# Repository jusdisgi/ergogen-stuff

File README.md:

# ergogen-stuff
My random ergogen files

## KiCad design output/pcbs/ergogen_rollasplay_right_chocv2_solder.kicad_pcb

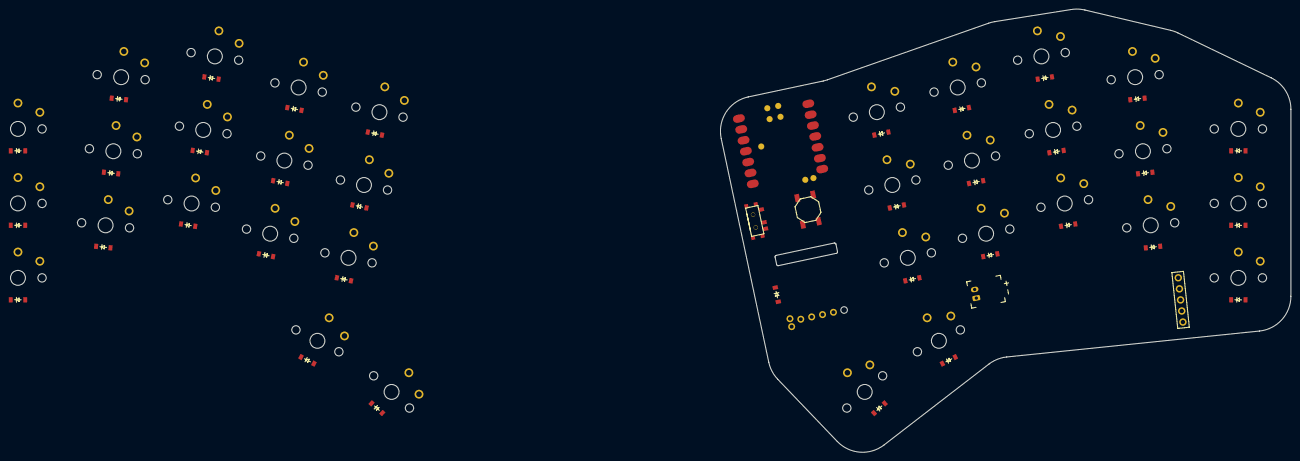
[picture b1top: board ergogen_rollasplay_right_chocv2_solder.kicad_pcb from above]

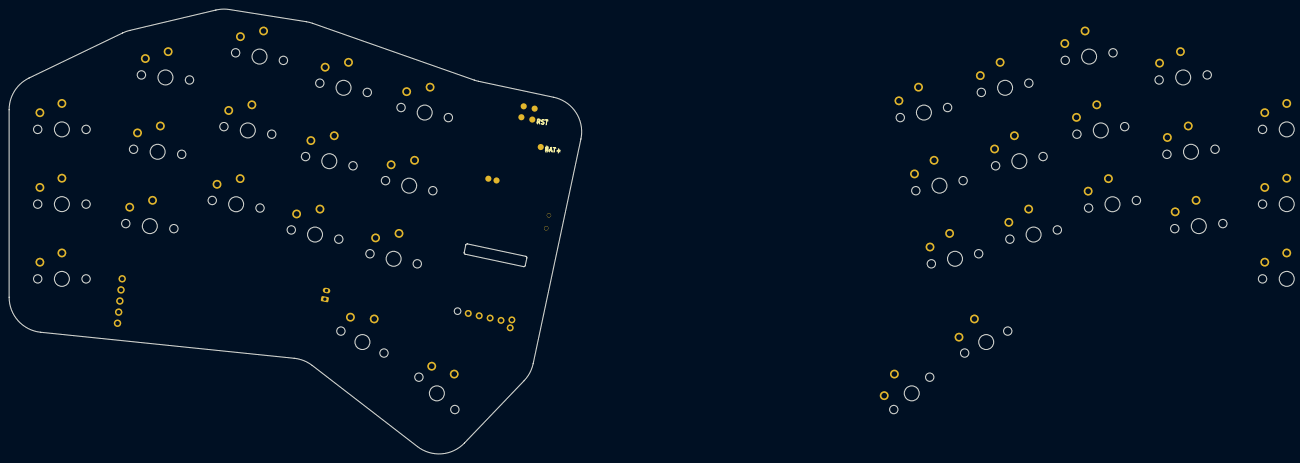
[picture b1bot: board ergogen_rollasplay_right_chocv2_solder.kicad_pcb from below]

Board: 2 copper layers, 130.2 x 101.2 mm, 74 parts (34 on the bottom side), 45 nets, no tracks yet.

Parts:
B1: SW_TACT_ALPS_SKQGABE010
D1, D2, D3, D4, D5, D6, D7, D8, D9, D10, D11, D12, D13, D14, D15, D16, D17, D18, D19, D20, D21, D22, D23, D24, D25, D26, D27, D28, D29, D30, D31, D32, D33, D34, D35: diode_tht_sod123
DISP1: display_nice_view
JST1: battery_connector_jst_ph_2
MCU1: xiao_smd
S1, S2, S3, S4, S5, S6, S7, S8, S9, S10, S11, S12, S13, S14, S15, S16, S17, S18, S19, S20, S21, S22, S23, S24, S25, S26, S27, S28, S29, S30, S31, S32, S33, S34: switch_choc_v1_v2
T1: SPDT_C128955

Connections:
D0: MCU1.1, S1.2, S2.2, S3.2, S30.2, S31.2, S32.2
D1: D3.1, D6.1, D9.1, D12.1, D15.1, MCU1.2, S27.2, S28.2, S29.2, S34.2
D2: MCU1.3, S4.2, S5.2, S6.2, S24.2, S25.2, S26.2, S33.2
D3: D2.1, D5.1, D8.1, D11.1, D14.1, MCU1.4, S21.2, S22.2, S23.2
D4: D18.1, D21.1, D24.1, D27.1, D30.1, MCU1.5, S7.2, S8.2, S9.2
D5: D1.1, D4.1, D7.1, D10.1, D13.1, D33.1, D34.1, D35.1, MCU1.6, S16.2
D8: MCU1.9, S10.2, S11.2, S12.2, S17.2, S18.2, S19.2, S20.2
D9: D19.1, D22.1, D25.1, D28.1, D31.1, MCU1.10, S13.2, S14.2, S15.2
D10: D16.1, D17.1, D20.1, D23.1, D26.1, D29.1, D32.1, MCU1.11
GND: B1.1, JST1.1, MCU1.13, MCU1.18
RST: B1.2, MCU1.17
far_onerow: D17.2, S17.1
index_bottom: D10.2, S10.1
index_home: D11.2, S11.1
index_top: D12.2, S12.1
inner_bottom: D13.2, S13.1
inner_home: D14.2, S14.1
inner_top: D15.2, S15.1
middle_bottom: D7.2, S7.1
middle_home: D8.2, S8.1
middle_top: D9.2, S9.1
mirror_far_onerow: D34.2, S34.1
mirror_index_bottom: D27.2, S27.1
mirror_index_home: D28.2, S28.1
mirror_index_top: D29.2, S29.1
mirror_inner_bottom: D30.2, S30.1
mirror_inner_home: D31.2, S31.1
mirror_inner_top: D32.2, S32.1
mirror_middle_bottom: D24.2, S24.1
mirror_middle_home: D25.2, S25.1
mirror_middle_top: D26.2, S26.1
mirror_near_onerow: D33.2, S33.1
mirror_pinky_bottom: D18.2, S18.1
mirror_pinky_home: D19.2, S19.1
mirror_pinky_top: D20.2, S20.1
mirror_ring_bottom: D21.2, S21.1
mirror_ring_home: D22.2, S22.1
mirror_ring_top: D23.2, S23.1
near_onerow: D16.2, S16.1
pinky_bottom: D1.2, S1.1
pinky_home: D2.2, S2.1
pinky_top: D3.2, S3.1
ring_bottom: D4.2, S4.1
ring_home: D5.2, S5.1
ring_top: D6.2, S6.1

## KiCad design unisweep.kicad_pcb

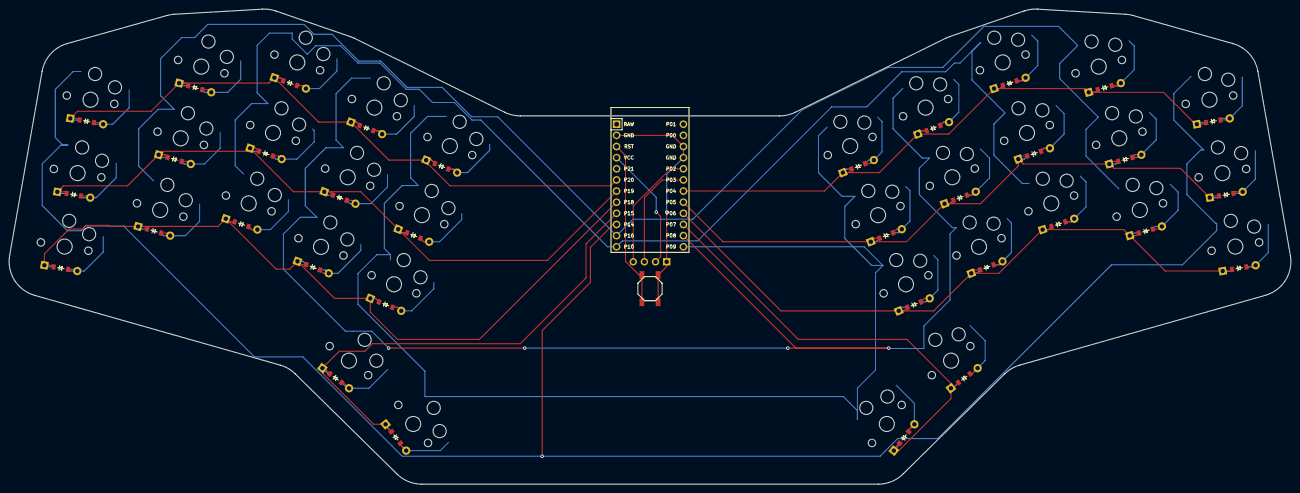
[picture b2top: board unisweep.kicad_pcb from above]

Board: 2 copper layers, 292.3 x 108.3 mm, 71 parts (0 on the bottom side), 52 nets.

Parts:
B1: SW_TACT_ALPS_SKQGABE010
D1, D2, D3, D4, D5, D6, D7, D8, D9, D10, D11, D12, D13, D14, D15, D16, D17, D18, D19, D20, D21, D22, D23, D24, D25, D26, D27, D28, D29, D30, D31, D32, D33, D34: ComboDiode
MCU1: ProMicro
OLED1: OLED; OLED_headers
S1, S2, S3, S4, S5, S6, S7, S8, S9, S10, S11, S12, S13, S14, S15, S16, S17, S18, S19, S20, S21, S22, S23, S24, S25, S26, S27, S28, S29, S30, S31, S32, S33, S34: PG1350

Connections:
GND: B1.1, MCU1.2, MCU1.15, MCU1.16, OLED1.1
P2: MCU1.17, OLED1.4
P3: MCU1.18, OLED1.3
P4: D20.1, D23.1, D26.1, D29.1, D32.1, MCU1.19
P5: D19.1, D22.1, D25.1, D28.1, D31.1, MCU1.20
P6: D18.1, D21.1, D24.1, D27.1, D30.1, MCU1.21
P7: D33.1, D34.1, MCU1.22
P8: MCU1.23, S10.1, S11.1, S12.1, S16.1, S27.1, S28.1, S29.1, S33.1
P9: MCU1.24, S13.1, S14.1, S15.1, S17.1, S30.1, S31.1, S32.1, S34.1
P10: MCU1.12, S7.1, S8.1, S9.1, S24.1, S25.1, S26.1
P14: MCU1.10, S1.1, S2.1, S3.1, S18.1, S19.1, S20.1
P15: D16.1, D17.1, MCU1.9
P16: MCU1.11, S4.1, S5.1, S6.1, S21.1, S22.1, S23.1
P18: D1.1, D4.1, D7.1, D10.1, D13.1, MCU1.8
P19: D2.1, D5.1, D8.1, D11.1, D14.1, MCU1.7
P20: D3.1, D6.1, D9.1, D12.1, D15.1, MCU1.6
RST: B1.2, MCU1.3
VCC: MCU1.4, OLED1.2
index_bottom: D10.2, S10.2
index_home: D11.2, S11.2
index_top: D12.2, S12.2
inner_bottom: D13.2, S13.2
inner_home: D14.2, S14.2
inner_top: D15.2, S15.2
left_onerow: D16.2, S16.2
middle_bottom: D7.2, S7.2
middle_home: D8.2, S8.2
middle_top: D9.2, S9.2
mirror_index_bottom: D27.2, S27.2
mirror_index_home: D28.2, S28.2
mirror_index_top: D29.2, S29.2
mirror_inner_bottom: D30.2, S30.2
mirror_inner_home: D31.2, S31.2
mirror_inner_top: D32.2, S32.2
mirror_left_onerow: D33.2, S33.2
mirror_middle_bottom: D24.2, S24.2
mirror_middle_home: D25.2, S25.2
mirror_middle_top: D26.2, S26.2
mirror_pinky_bottom: D18.2, S18.2
mirror_pinky_home: D19.2, S19.2
mirror_pinky_top: D20.2, S20.2
mirror_right_onerow: D34.2, S34.2
mirror_ring_bottom: D21.2, S21.2
mirror_ring_home: D22.2, S22.2
mirror_ring_top: D23.2, S23.2
pinky_bottom: D1.2, S1.2
pinky_home: D2.2, S2.2
pinky_top: D3.2, S3.2
right_onerow: D17.2, S17.2
ring_bottom: D4.2, S4.2
ring_home: D5.2, S5.2
ring_top: D6.2, S6.2

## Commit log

2025-04-10 New version including right half.
2025-04-13 Create several variations on rollasplay, add footprints.
2025-04-13 Unbork main/master branching.
2025-04-13 Rename pg1316s footprint to add verbosity; still does not yet work.
